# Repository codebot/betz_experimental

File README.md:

# greetings
This repo is an experimental collection of firmware and software for the
Betz drive, with emphasis on real-time control frequency and reducing
current control noise. The firmware is currently written bare-metal on
the STM32, without an OS or platform library of any sort.

# notes
 * MCU: STM32F405RG

# getting ready
Because the `betz_mini` board is designed around STM32G4, it needs the
latest `openocd`, rather than what is distributed with Ubuntu 18.04. To
build `openocd` and install it into `/usr/local` :
```
sudo apt install gcc-arm-none-eabi

mkdir ~/tools
cd ~/tools
git clone git://repo.or.cz/openocd.git
cd openocd
./bootstrap
./configure
make
sudo make install
```

If you want to flash firmware directly to the board, and you don't have
a udev rule set up yet for your SWD programmer, you'll need something
like this (the VID/PID is for the Olimex USB-TINY-H programmer):
```
ACTION=="add", ATTR{idVendor}=="0403", ATTR{idProduct}=="6010", MODE:="666"
```
then run `sudo udevadm trigger` to reload the rules.

# compiling firmware
```
cd firmware
mkdir build
cd build
cmake ..
make
```

# flashing stuff
First, connect a SWD programmer to the header on the board. If it doesn't
exist already, add an appropriate rule in `/etc/udev/rules.d` so you don't
need `sudo` to access the device. Then, from the firmware `build` directory:

```
make PROGRAM.flash_swd
```

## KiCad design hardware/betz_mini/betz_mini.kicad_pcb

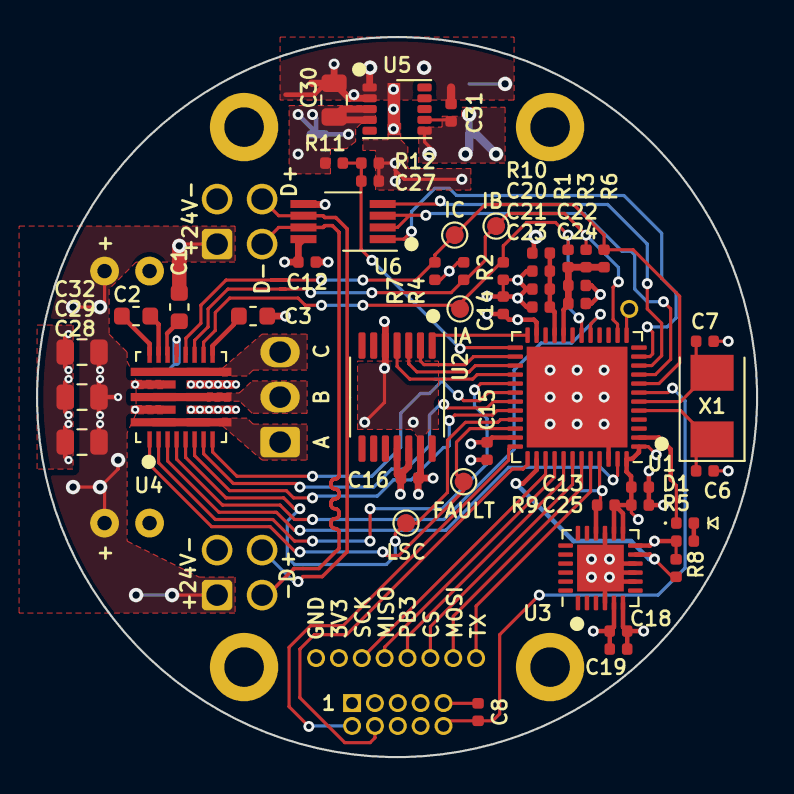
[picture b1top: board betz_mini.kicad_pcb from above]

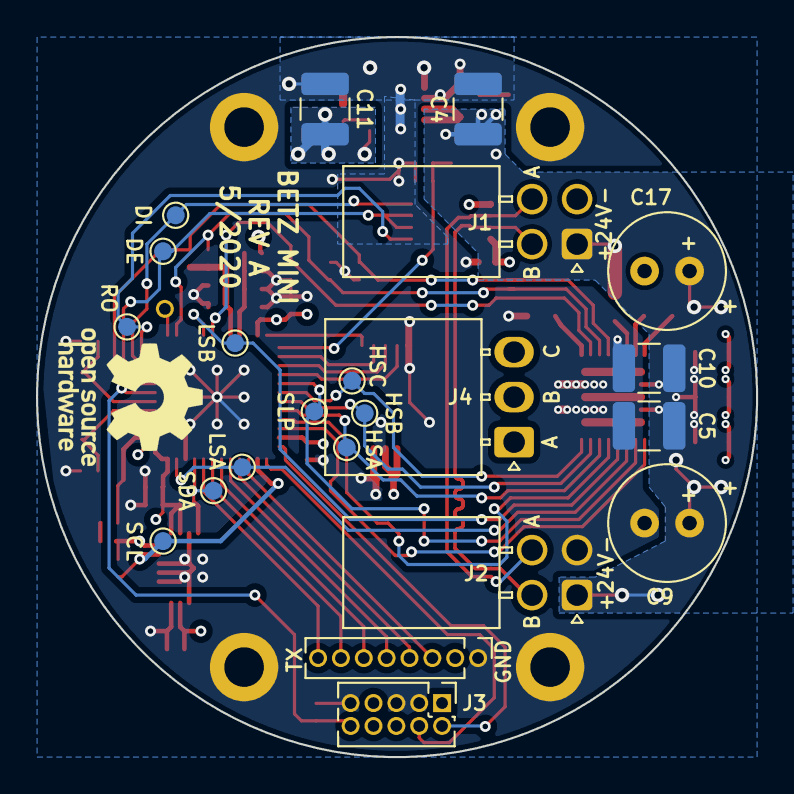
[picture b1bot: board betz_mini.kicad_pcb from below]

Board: 4 copper layers, 40.0 x 40.0 mm, 78 parts (24 on the bottom side), 49 nets.

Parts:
C1: 1u; C_0603_1608Metric
C2: 100n; C_0603_1608Metric
C3: 4u7; C_0603_1608Metric
C4, C5, C10: 10u; C_1210_3225Metric
C6, C7: 15p; C_0402_1005Metric
C8, C12, C13, C14, C15, C16, C18, C23, C24, C27: 100n; C_0402_1005Metric
C9, C17: 100u; C_Radial_D6.3mm_H11.0mm_P2.50mm
C11: 47u; C_1210_3225Metric
C19, C21, C22: 1u; C_0402_1005Metric
C20, C25, C31: 10u; C_0402_1005Metric
C28, C29, C30, C32: 4u7; C_0805_2012Metric
D1: status; LED_0402_1005Metric
H1, H2, H3, H4: MountingHole_Pad; MountingHole_2.2mm_M2_DIN965_Pad
J1: upstream; Molex_Nano-Fit_105314-xx04_2x02_P2.50mm_Horizontal
J2: downstream; Molex_Nano-Fit_105314-xx04_2x02_P2.50mm_Horizontal
J3: ARM SWD; PinHeader_2x05_P1.27mm_Vertical
J4: BLDC; Molex_Nano-Fit_105313-xx03_1x03_P2.50mm_Horizontal
J5: BONUS; PinHeader_1x08_P1.27mm_Vertical
J6: EXTRA_BONUS; PinHeader_1x01_P1.27mm_Vertical
LOGO1: Logo_Open_Hardware_Small; OSHW-Logo_7.5x8mm_SilkScreen
R1, R2, R3, R4, R6, R7, R8, R9, R12: 4k7; R_0402_1005Metric
R5: 330; R_0402_1005Metric
R10: ferrite; R_0402_1005Metric
R11: 100k; R_0402_1005Metric
TP1, TP2, TP3, TP4, TP5, TP6, TP7, TP8, TP9, TP10, TP11, TP12, TP13, TP14, TP15, TP16: TestPoint_Small; TestPoint_Pad_D1.0mm
U1: stm32g474ceu6; QFN-48-1EP_7x7mm_P0.5mm_EP5.6x5.6mm
U2: AS5047U; TSSOP-14_4.4x5mm_P0.65mm
U3: IIS328DQ; QFN-24-1EP_4x4mm_P0.5mm_EP2.6x2.6mm
U4: MP6540
U5: LMZM23601V3; Texas_SIL0010A_MicroSiP-10-1EP_3.8x3mm_P0.6mm_EP0.7x2.9mm_T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
U6: THVD2450; VSSOP-8_3.0x3.0mm_P0.65mm
X1: 8 MHz; Crystal_SMD_5032-2Pin_5.0x3.2mm

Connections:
+3V3: C11.1, C12.1, C13.1, C14.1, C15.1, C16.1, C18.1, C19.1, C25.1, C31.1, J3.1 (VTref), J5.2, R5.2, R8.1, R9.1, R10.1, U1.1 (VBAT), U1.23 (VDD), U1.35 (VDD), U1.48 (VDD), U2.11 (VDD5V), U2.12 (VDD3V), U3.5 (VDD), U3.12 (CS), U3.13 (RSVD_VDD), U3.14 (VDD_IO), U5.6 (VOUT), U5.7 (FB), U6.8 (VCC)
/ACCEL_SCL: R8.2, TP7.1, U1.38 (PA15), U3.11 (SCL)
/ACCEL_SDA: R9.2, TP8.1, U1.45 (PB7), U3.16 (SDA)
/BONUS_CS: J5.6, U1.42 (PB4)
/BONUS_GPIO: J5.5, U1.41 (PB3)
/BONUS_MISO: J5.4, U1.40 (PC11)
/BONUS_MOSI: J5.7, U1.43 (PB5)
/BONUS_SCK: J5.3, U1.39 (PC10)
/CP1: C2.1, U4.20 (CP1)
/CP2: C2.2, U4.21 (CP2)
/DEBUG_TX: J5.8, U1.44 (PB6)
/ENC_CS: U1.24 (PB11), U2.1 (CS)
/ENC_MISO: U1.27 (PB14), U2.3 (MISO)
/ENC_MOSI: U1.28 (PB15), U2.4 (MOSI)
/ENC_SCK: U1.26 (PB13), U2.2 (SCLK)
/FAULT: TP16.1, U1.34 (PA12), U4.1 (~FAULT)
/HSA: TP13.1, U1.32 (PA10), U4.6 (PWMA/HSA)
/HSB: TP14.1, U1.31 (PA9), U4.7 (PWMB/HSB)
/HSC: TP15.1, U1.30 (PA8), U4.8 (PWMC/HSC)
/IA: R1.2, R2.1, TP1.1, U1.18 (PB1), U4.15 (SOA)
/IB: R3.2, R4.1, TP2.1, U1.14 (PA6), U4.16 (SOB)
/IC: R6.2, R7.1, TP3.1, U1.8 (PA0), U4.17 (SOC)
/LSA: TP10.1, U1.47 (PB9), U4.3 (ENA/LSA)
/LSB: TP11.1, U1.17 (PB0), U4.4 (ENB/LSB)
/LSC: TP12.1, U1.33 (PA11), U4.5 (ENC/LSC)
/NRST: C8.1, J3.10 (~RESET~), U1.7 (PG10/NRST)
/PA5: J6.1, U1.13 (PA5)
/RS485+: J1.4, J2.4, U6.6 (A)
/RS485-: J1.3, J2.3, U6.7 (B)
/RS485_DE: TP5.1, U1.9 (PA1), U6.2 (~RE), U6.3 (DE)
/RS485_DI: TP6.1, U1.10 (PA2), U6.4 (DI)
/RS485_RO: TP4.1, U1.11 (PA3), U6.1 (RO)
/SA: J4.1, U4.9 (SA), U4.26 (SA)
/SB: J4.2, U4.11 (SB), U4.24 (SB)
/SC: J4.3, U4.13 (SC), U4.22 (SC)
/SLEEP: TP9.1, U1.29 (PC6), U4.2 (~SLEEP)
/STATUS_LED: D1.1 (K), U1.2 (PC13)
/SWCLK: J3.4 (SWDCLK/TCK), U1.37 (PA14)
/SWDIO: J3.2 (SWDIO/TMS), U1.36 (PA13)
/VBUS_DIV: C27.1, R11.2, R12.1, U1.25 (PB12)
/VCP: C1.2, U4.19 (VCP)
/VG: C3.1, U4.14 (VG)
/VREF: C22.1, C24.1, R1.1, R3.1, R6.1, U1.20 (VREF+)
GND: C3.2, C4.2, C5.2, C6.2, C7.2, C8.2, C9.2, C10.2, C11.2, C12.2, C13.2, C14.2, C15.2, C16.2, C17.2, C18.2, C19.2, C20.2, C21.2, C22.2, C23.2, C24.2, C25.2, C27.2, C28.2, C29.2, C30.2, C31.2, C32.2, H1.1, H2.1, H3.1, H4.1, J1.2, J2.2, J3.3 (GND), J3.5 (GND), J3.9 (GNDDetect), J5.1, R2.2, R4.2, R7.2, R12.2, U1.46 (PB8/BOOT0), U1.49 (PAD), U2.5 (TEST), U2.13 (GND), U3.4 (RSVD_GND), U3.6 (GND), U3.8 (GND), U3.9 (GND), U3.10 (GND), U3.15 (SA0), U3.25 (PAD), U4.10 (LSS), U4.12 (LSS), U4.18 (GND), U5.1 (GND), U5.2 (MODE/SYNC), U5.11 (GND), U6.5 (GND)
unnamed: C6.1, U1.5 (PF0/OSC_IN), X1.1
unnamed: C7.1, U1.6 (PF1/OSC_OUT), X1.2
unnamed: C20.1, C21.1, C23.1, R10.2, U1.21 (VDDA)
unnamed: D1.2 (A), R5.1
VBUS: C1.1, C4.1, C5.1, C9.1, C10.1, C17.1, C28.1, C29.1, C30.1, C32.1, J1.1, J2.1, R11.1, U4.23 (VIN), U4.25 (VIN), U5.3 (VIN), U5.4 (EN)

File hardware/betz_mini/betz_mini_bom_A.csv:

Component,Quantity Per PCB,References,Value,Footprint,MFN,MPN,D1N,D1PN
1,10,C8 C12 C13 C14 C15 C16 C18 C23 C24 C27,100n,C_0402_1005Metric,Samsung,CL05B104KO5NNNC,Digikey,1276-1001-1-ND
2,1,C2,100n,C_0603_1608Metric,TDK,CGA3E2X7R1H104K080AA,Digikey,445-5666-1-ND
3,2,C9 C17,100u,C_Radial_D6.3mm_H11.0mm_P2.50mm,DNP,DNP,DNP,DNP
4,3,C4 C5 C10,10u,C_1210_3225Metric,Samsung,CL32B106KBJNNWE,Digikey,1276-3388-1-ND
5,3,C20 C25 C31,10u,C_0402_1005Metric,Samsung,CL05A106MP5NUNC,Digikey,1276-1450-1-ND
6,2,C6 C7,15p,C_0402_1005Metric,Murata,GJM1555C1H150GB01D,Digikey,490-8080-1-ND
7,1,C1,1u,C_0603_1608Metric,Samsung,CL10B105MO8NNWC,Digikey,1276-6524-1-ND
8,3,C19 C21 C22,1u,C_0402_1005Metric,Samsung,CL05A105KP5NNNC,Digikey,1276-1076-1-ND
9,1,C11,47u,C_1210_3225Metric,Samsung,CL32A476MPJNNNE,Digikey,1276-3380-1-ND
10,4,C28 C29 C30 C32,4u7,C_0805_2012Metric,Samsung,CL21A475KBQNNNE,Digikey,1276-1248-1-ND
11,1,C3,4u7,C_0603_1608Metric,Samsung,CL10A475KA8NQNC,Digikey,1276-1900-1-ND
12,1,D1,status,LED_0402_1005Metric,Wurth,150040VS73240,Digikey,732-11992-1-ND
13,1,J3,ARM SWD,PinHeader_2x05_P1.27mm_Vertical,DNP,DNP,DNP,DNP
14,1,J4,BLDC,Molex_Nano-Fit_105313-xx03_1x03_P2.50mm_Horizontal,DNP,DNP,DNP,DNP
15,1,J5,BONUS,PinHeader_1x08_P1.27mm_Vertical,DNP,DNP,DNP,DNP
16,1,J6,EXTRA_BONUS,PinHeader_1x01_P1.27mm_Vertical,DNP,DNP,DNP,DNP
17,2,J1 J2,upstream,Molex_Nano-Fit_105314-xx04_2x02_P2.50mm_Horizontal,DNP,DNP,DNP,DNP
18,1,LOGO1,Logo_Open_Hardware_Small,OSHW-Logo_7.5x8mm_SilkScreen,DNP,DNP,DNP,DNP
19,1,R11,100k,R_0402_1005Metric,Panasonic,ERJ-2GEJ104X,Digikey,P100KJCT-ND
20,1,R5,330,R_0402_1005Metric,Panasonic,ERJ-2GEJ331X,Digikey,P330JCT-ND
21,9,R1 R2 R3 R4 R6 R7 R8 R9 R12,4k7,R_0402_1005Metric,Panasonic,ERJ-2RKF4701X,Digikey,P4.70KLCT-ND
22,1,R10,ferrite,R_0402_1005Metric,Murata,BLM15AG601SN1D,Digikey,490-1006-1-ND
23,1,U2,AS5047U,TSSOP-14_4.4x5mm_P0.65mm,AMS,AS5047U-HTSM,Mouser,985-AS5047U-HTSM
24,1,U3,IIS328DQ,QFN-24-1EP_4x4mm_P0.5mm_EP2.6x2.6mm,ST,497-15701-1-ND,Digikey,497-15701-1-ND
25,1,U5,LMZM23601V3,Texas_SIL0010A_MicroSiP-10-1EP_3.8x3mm_P0.6mm_EP0.7x2.9mm_ThermalVias,TI,LMZM23601V3SILT,Digikey,296-49461-1-ND
26,1,U4,MP6540,MP6540,MPS,MP6540AGU,Mouser,946-MP6540AGU-P
27,1,U6,THVD2450,VSSOP-8_3.0x3.0mm_P0.65mm,TI,THVD2450DGKR,Digikey,296-THVD2450DGKRCT-ND
28,1,U1,stm32g474ceu6,QFN-48-1EP_7x7mm_P0.5mm_EP5.6x5.6mm,ST,STM32G474CEU6,Digikey,497-STM32G474CEU6-ND
29,1,X1,8 MHz,Crystal_SMD_5032-2Pin_5.0x3.2mm,Abracon,ABM3-8.000MHZ-D2Y-T,Digikey,535-10630-1-ND





Component Groups:,29
Component Count:,58
Fitted Components:,58
Number of PCBs:,1
Total components:,58
Schematic Version:,A
Schematic Date:,2020-04-25
PCB Variant:,['default']
BoM Date:,Sun May  3 23:17:22 2020
Schematic Source:,/home/mquigley/hw/betz_experimental/hardware/betz_mini/betz_mini.sch
KiCad Version:,Eeschema 5.99.0-unknown-7e1294a~101~ubuntu18.04.1

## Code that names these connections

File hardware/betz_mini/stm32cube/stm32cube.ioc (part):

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PA6.Mode=IN3-Single-Ended
Mcu.UserName=STM32G474CEUx
PC10.Signal=SPI3_SCK
PA11.Mode=Output Compare1 CH1 CH1N
PB11.Signal=GPIO_Output
PB13.Signal=SPI2_SCK
PB15.Signal=SPI2_MOSI
PA12.Signal=GPIO_Input
PB6.Signal=USART1_TX
RCC.HSE_VALUE=8000000
PA15.Mode=I2C
PA14.Mode=Serial_Wire
PB14.Mode=Full_Duplex_Master
PB5.Mode=Full_Duplex_Master
PA0.Mode=IN1-Single-Ended
PB7.Signal=I2C1_SDA
PA8.Signal=S_TIM1_CH1
PA0.Signal=ADC1_IN1
Mcu.Package=UFQFPN48
PB9.Signal=TIM1_CH3N
PB1.Signal=ADC3_IN1
PA6.Signal=ADC2_IN3
PB12.Mode=IN3-Single-Ended
PA10.Signal=S_TIM1_CH3
PA15.Signal=I2C1_SCL
PC11.Mode=Full_Duplex_Master
PB13.Mode=Full_Duplex_Master
PF1-OSC_OUT.Mode=HSE-External-Oscillator
PF1-OSC_OUT.Signal=RCC_OSC_OUT
PB4.Signal=GPIO_Output
PA3.Signal=USART2_RX
PC13.Signal=TIM8_CH4N
PC11.Signal=SPI3_MISO
PC6.Signal=GPIO_Output
PC10.Mode=Full_Duplex_Master
PA13.Signal=SYS_JTMS-SWDIO
PA3.Mode=Asynchronous
PB9.Mode=Output Compare3 CH3 CH3N
PA9.Signal=S_TIM1_CH2
PA1.Signal=USART2_DE
PF0-OSC_IN.Mode=HSE-External-Oscillator
PB14.Signal=SPI2_MISO
PB0.Mode=Output Compare2 CH2 CH2N
board=custom
PB15.Mode=Full_Duplex_Master
PA1.Mode=Hardware Flow Control (RS485)
PC13.Mode=PWM Generation4 CH4N
PA13.Mode=Serial_Wire
Mcu.Name=STM32G474C(B-C-E)Ux
PA2.Signal=USART2_TX
PB3.Signal=GPIO_Output
RCC.SYSCLKFreq_VALUE=16000000
PB5.Signal=SPI3_MOSI
PB7.Mode=I2C
PA11.Signal=TIM1_CH1N
PA14.Signal=SYS_JTCK-SWCLK
PB1.Mode=IN1-Single-Ended
PA2.Mode=Asynchronous
PF0-OSC_IN.Signal=RCC_OSC_IN
PB0.Signal=TIM1_CH2N
PB12.Signal=ADC4_IN3

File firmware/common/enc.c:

/*
 * Copyright (C) 2020 Open Source Robotics Foundation
 *
 * Licensed under the Apache License, Version 2.0 (the "License");
 * you may not use this file except in compliance with the License.
 * You may obtain a copy of the License at
 *
 *     http://www.apache.org/licenses/LICENSE-2.0
 *
 * Unless required by applicable law or agreed to in writing, software
 * distributed under the License is distributed on an "AS IS" BASIS,
 * WITHOUT WARRANTIES OR CONDITIONS OF ANY KIND, either express or implied.
 * See the License for the specific language governing permissions and
 * limitations under the License.
 *
*/

#if defined(BOARD_blue)

// PB9 = SPI CS  as GPIO
// PC10 = SPI3 CLK  as AF6
// PC11 = SPI3 MISO as AF6
// PC12 = SPI3 MOSI as AF6

#define ENC_SPI SPI3
#define ENC_AF 6
#define ENC_IRQ SPI3_IRQn
#define ENC_VECTOR spi3_vector

#define ENC_CS_GPIO   GPIOB
#define ENC_SCLK_GPIO GPIOC
#define ENC_MOSI_GPIO GPIOC
#define ENC_MISO_GPIO GPIOC

#define ENC_CS_PIN    9
#define ENC_SCLK_PIN 10
#define ENC_MISO_PIN 11
#define ENC_MOSI_PIN 12

#elif defined(BOARD_mini)

#define ENC_SPI SPI2
#define ENC_AF 5
#define ENC_IRQ SPI2_IRQn
#define ENC_VECTOR spi2_vector

#define ENC_CS_GPIO   GPIOB
#define ENC_SCLK_GPIO GPIOB
#define ENC_MISO_GPIO GPIOB
#define ENC_MOSI_GPIO GPIOB

#define ENC_CS_PIN   11
#define ENC_SCLK_PIN 13
#define ENC_MISO_PIN 14
#define ENC_MOSI_PIN 15

#endif


#include <stdio.h>
#include <math.h>

#include "soc.h"

#include "enc.h"
#include "param.h"
#include "pin.h"
#include "state.h"

volatile float g_encoder_offset = 0;
volatile int g_encoder_dir = 0;

void enc_init()
{
  param_float(
      "encoder_offset",
      &g_encoder_offset,
      100,
      PARAM_PERSISTENT);

  param_int(
      "encoder_dir",
      &g_encoder_dir,
      1,
      PARAM_PERSISTENT);

  pin_set_output(ENC_CS_GPIO, ENC_CS_PIN, 1);
  pin_set_alternate_function(ENC_SCLK_GPIO, ENC_SCLK_PIN, ENC_AF);
  pin_set_alternate_function(ENC_MISO_GPIO, ENC_MISO_PIN, ENC_AF);
  pin_set_alternate_function(ENC_MOSI_GPIO, ENC_MOSI_PIN, ENC_AF);

  pin_set_output_speed(ENC_CS_GPIO, ENC_CS_PIN, 1);
  pin_set_output_speed(ENC_SCLK_GPIO, ENC_SCLK_PIN, 1);
  pin_set_output_speed(ENC_MISO_GPIO, ENC_MISO_PIN, 1);
  pin_set_output_speed(ENC_MOSI_GPIO, ENC_MOSI_PIN, 1);

#if defined(BOARD_blue)
  RCC->APB1ENR |= RCC_APB1ENR_SPI3EN;
#elif defined(BOARD_mini)
  RCC->APB1ENR1 |= RCC_APB1ENR1_SPI2EN;
#endif

  ENC_SPI->CR1 =
      SPI_CR1_CPHA |  // clock phase: cpha=1, cpol=0
      SPI_CR1_MSTR |  // master mode
      SPI_CR1_SSM  |  // set software slave select pin management
      SPI_CR1_SSI  ;  // assert software SSI pin

#if defined(BOARD_blue)

  // APB1 clock is 168/4 = 42 MHz
  // AS5047U max SPI rate is 10 MHz, so we have to use 42/8 = 5.25 MHz

  ENC_SPI->CR1 |=
      SPI_CR1_DFF  |  // 16 bit data frames
      SPI_CR1_BR_1 ;  // BR[2:0] = 010b  to divide PCLK by 8 = 5.25 MHz

#elif defined(BOARD_mini)

  // APB1 clock is 168 MHz
  // AS5047U max SPI rate is 10 MHz, so we need 168/32 = 5.25 MHz

  ENC_SPI->CR1 |=
      SPI_CR1_BR_2;  // BR[2:0] = 100b  to divide PCLK by 32 = 5.25 MHz

  ENC_SPI->CR2 |=
      (0xf << SPI_CR2_DS_Pos);  // DS[3:0] = 0xf  for 16-bit data transfers

#endif

  ENC_SPI->CR2 |= SPI_CR2_RXNEIE;  // enable receive interrupt
  ENC_SPI->CR1 |= SPI_CR1_SPE;  // enable SPI

  NVIC_SetPriority(ENC_IRQ, 3);  // lower than PWM and comms priority
  NVIC_EnableIRQ(ENC_IRQ);
}

uint16_t enc_read_pos_blocking()
{
  NVIC_DisableIRQ(ENC_IRQ);
  pin_set_output_low(ENC_CS_GPIO, ENC_CS_PIN);

  ENC_SPI->DR;  // flush RX with a dummy read
  ENC_SPI->DR = 0xffff;
  while (!(ENC_SPI->SR & SPI_SR_RXNE)) { }  // wait for it...

  pin_set_output_high(ENC_CS_GPIO, ENC_CS_PIN);

  uint16_t reading = ENC_SPI->DR & 0x3fff;  // returns the _previous_ read
  if (g_encoder_dir < 0)
    reading = 16383 - reading;

  NVIC_EnableIRQ(ENC_IRQ);

  return reading;
}

void enc_blocking_read_to_state()
{
  g_state.enc = enc_read_pos_blocking();
}

void enc_start_nonblocking_read_to_state()
{
  pin_set_output_low(ENC_CS_GPIO, ENC_CS_PIN);
  ENC_SPI->DR = 0xffff;
}

void ENC_VECTOR()
{
  pin_set_output_high(ENC_CS_GPIO, ENC_CS_PIN);
  const uint16_t pos_raw = ENC_SPI->DR & 0x3fff;  // returns the previous read
  float pos = pos_raw * (float)(2.0 * M_PI / 16384.0);

  if (g_encoder_dir < 0)
    pos *= -1.0f;

  pos += g_encoder_offset;

  if (pos < 0)
    pos += (float)(2 * M_PI);
  else if (pos > (float)(2 * M_PI))
    pos -= (float)(2 * M_PI);

  g_state.enc = pos;
}

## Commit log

2020-03-13 startup skeleton
2020-03-20 led blinking, hooray
2020-03-20 hello world
2020-03-20 add rs485 skeleton
2020-03-23 rs485 timing
2020-03-23 bringing up more peripherals and WIP bootloader
2020-03-24 adding address options to protocol
2020-03-25 gradually putting some structure in
2020-03-27 bump rs485 bitrate up to 3mbit
2020-04-06 WIP parser
2020-04-09 skeleton of a comms emulator project
2020-04-10 isolating rs485 from the comms stack to allow emulation
2020-04-10 WIP emulator comms
2020-04-10 C mcast tx appearing to work
2020-04-10 separate transport from bus class
2020-04-11 WIP multicast transport for dev/testing on driver node
2020-04-11 WIP multicast comms
2020-04-15 implementing packet protocol for multicast loopback
2020-04-15 WIP discovery comms
2020-04-16 WIP comms
2020-04-17 WIP discovery and enumeration
2020-04-20 add rng support
2020-04-20 rs485 bias testing and RNG testing
2020-04-24 add random delays to comms discovery requests. start adding licenses
2020-04-24 WIP discovery
2020-04-25 WIP small driver board
2020-04-26 WIP. 35mm square
2020-04-26 WIP detailing schematic and placement
2020-04-27 WIP schematic
2020-04-27 WIP awesome
2020-04-28 WIP betz mini
2020-04-28 start route of power section
2020-04-29 rev.A first pass complete
2020-04-29 image
2020-04-30 update part numbers
2020-04-30 WIP bootloader
2020-05-01 route low-side pwm so that MP6540A can also work on this board
2020-05-03 bootloader starting to work HOORAY
2020-05-03 bootloader
2020-05-03 encoder test application
2020-05-03 pwm driver
2020-05-03 hopefully last bit of PCB cleanup.
2020-05-04 rev.A sent out for quote
2020-05-04 beginnings of a C++ Qt GUI
2020-05-04 fix up emulator
2020-05-04 WIP packet listener in GUI
2020-05-05 WIP param GUI
2020-05-06 WIP parameter setting from GUI
2020-05-06 fix cmake for qwt
2020-05-06 WIP state stream to GUI
2020-05-06 WIP state polling
2020-05-07 nonblocking encoder reads and data streaming to GUI
2020-05-08 hooray, starting to spin
2020-05-09 WIP write parameters to flash
2020-05-10 WIP flash param
2020-05-11 write param table
2020-05-12 load params from flash on startup
2020-05-12 minimalist position controller
2020-05-18 working towards multiple build targets for firmware
2020-05-21 working towards adding stm32g4 mini board
2020-05-22 bringing up a new mcu is always an adventure
2020-05-22 it blinks
2020-05-22 stm32g4 console OK
2020-05-22 bringing up systime and rs485
2020-05-24 bring up flash driver and bootloader
2020-05-25 bringing up pwm on stm32g
2020-05-25 port pwm and encoder driver to stm32g4 board
2020-05-25 towards adc driver
2020-05-26 mini board spins, hooray
2020-06-02 WIP param table for stm32g4
2020-06-02 skeleton of new flash driver
2020-06-02 WIP flash driver and reviving emulator
2020-06-02 emulator compiles, hooray
2020-06-03 emulator appears to work with latest param code
2020-06-03 hunt down and defeat a bug that was latching USART overrun
2020-06-04 enable RNG clock in STM32G4
2020-06-07 reduce functionality of bootloader to only flash programming
2020-06-08 default to idle mode. add boot button to GUI
2020-06-13 don't crash if there isn't an IP address
2020-06-13 generate unique flash filename from serial number of emulator instance
2020-06-15 wip emulator
2020-06-17 multi-drive param GUI starting to be OK
2020-06-18 reorg to allow external driver library linkage
2020-06-19 set position target
2020-06-20 special-case id param and save it for later
2020-06-21 add function to get drives by id
2020-06-23 add velocity damping and position/velocity filtering
2020-07-06 send effort in state poll message. start on calibration.
2020-07-06 add integrator and unwrapping
2020-07-07 working on decogging
2020-07-08 use loess to make a fairly decent approximation
2020-07-08 store a cog table in the parameters flash area and use it
2020-07-09 nonsense
2020-07-11 dataset collection routing for calibrating encoder offest
2020-12-02 velocity controller
